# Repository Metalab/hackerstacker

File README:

Hacker Stacker Stacker Hacker
=============

stacker. stacker. STACKER.

You know the game..
Now go build your own with an arduino and 2 x RGB-123
Its fun and addictive.

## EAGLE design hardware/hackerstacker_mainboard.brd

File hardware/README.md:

The eagle files for the mainboard..

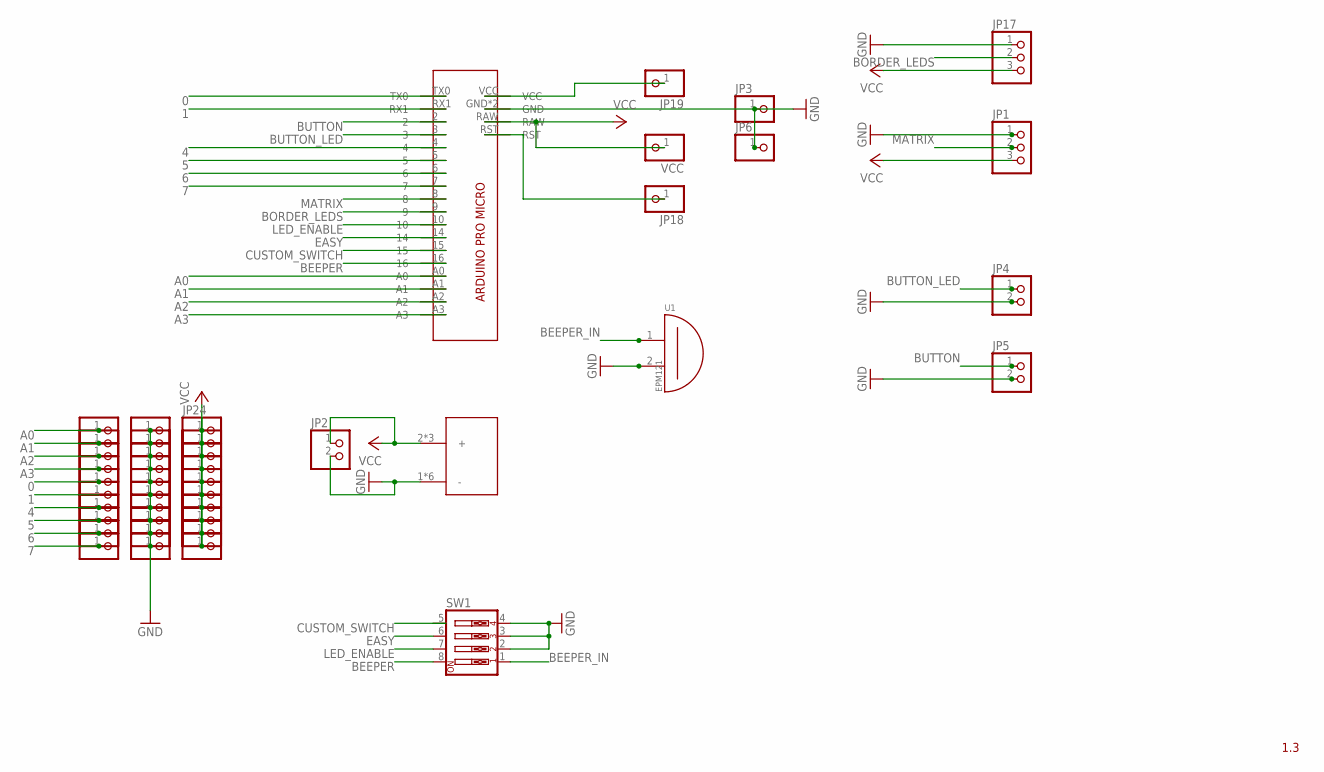
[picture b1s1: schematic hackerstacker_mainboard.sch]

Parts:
JP1, JP17: PINHD-1X3; 1X03
JP2, JP4, JP5: PINHD-1X2; 1X02
JP3, JP6, JP7, JP8, JP9, JP10, JP11, JP12, JP13, JP14, JP15, JP16, JP18, JP19, JP20, JP21, JP22, JP23, JP24, JP25, JP26, JP27, JP28, JP29, JP30, JP31, JP32, JP33, JP34, JP35, JP36, JP37, JP38, JP39: PINHD-1X1CB; 1X01-CLEANBIG
SW1: SW_DIP-4; EDG-04
U1: EPM121
U$1: ARDUINO_PRO_MICRO; APM_PAC
U$3: 2.1MMARDUINOPOERJACK; POWERSUPPLY_DC-21MM
VCC: PINHD-1X1CB; 1X01-CLEANBIG

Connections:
0: JP11.1, U$1.TX0
1: JP12.1, U$1.RX1
4: JP13.1, U$1.4
5: JP37.1, U$1.5
6: JP38.1, U$1.6
7: JP39.1, U$1.7
A0: JP7.1, U$1.A0
A1: JP8.1, U$1.A1
A2: JP9.1, U$1.A2
A3: JP31.1, U$1.A3
BEEPER: SW1.8, U$1.16
BEEPER_IN: SW1.1, U1.1
BORDER_LEDS: JP17.2, U$1.9
BUTTON: JP5.1, U$1.2
BUTTON_LED: JP4.1, U$1.3
CUSTOM_SWITCH: SW1.5, U$1.15
EASY: SW1.6, U$1.14
GND: JP1.1, JP2.2, JP3.1, JP4.2, JP5.2, JP6.1, JP14.1, JP15.1, JP16.1, JP17.1, JP20.1, JP21.1, JP22.1, JP23.1, JP34.1, JP35.1, JP36.1, SW1.2, SW1.3, SW1.4, U1.2, U$1.GND, U$1.GND2 (GND), U$3.1 (-), U$3.3 (-), U$3.4 (-), U$3.5 (-), U$3.6 (-), U$3.7 (-)
LED_ENABLE: SW1.7, U$1.10
MATRIX: JP1.2, U$1.8
unnamed: JP18.1, U$1.RST
unnamed: JP19.1, U$1.VCC
VCC: JP1.3, JP2.1, JP10.1, JP17.3, JP24.1, JP25.1, JP26.1, JP27.1, JP28.1, JP29.1, JP30.1, JP32.1, JP33.1, U$1.RAW, U$3.2 (+), U$3.8 (+), U$3.9 (+), VCC.1

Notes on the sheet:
1.3

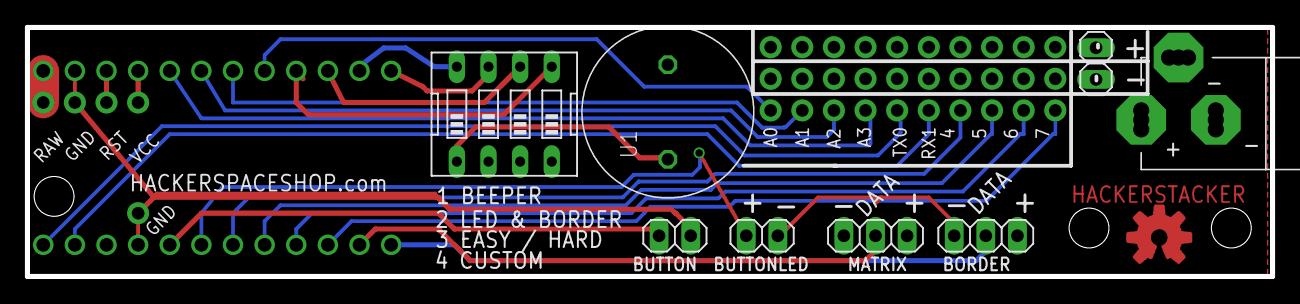
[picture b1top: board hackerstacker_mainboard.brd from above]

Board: 2 copper layers, 100.0 x 20.0 mm, 45 parts (0 on the bottom side), 23 nets.

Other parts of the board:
U$4: OSHWLOGO_TOP_0.2

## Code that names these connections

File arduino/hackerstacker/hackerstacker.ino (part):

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//these pin definitions are valid for arduino pro MICRO (the one with USB

// where is the matrix?
#define MATRIX_PIN 8

// where is the BUTTON?
// needs to be interrupt enabled pin
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#define GAME_BRIGHTNESS 40

// the second dip switch that controls wether the border  and the button should be iluminated or not
#define LED_ENABLE 10

// the third dip switch that controls if the game should be easy or hard TODO: implement this.
#define EASY_HARD 14

// the fourth  dip switch that can be used for custom input .. for example a mode that makes the game unbeatable or something.. 
#define CUSTOM_SWITCH 15

// on board led
#define ONBOARD_LED 17
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// There's only one row here, so it doesn't matter if we declare it in row
// or column order.  The matrices use 800 KHz (v2) pixels that expect GRB
// color data.
Adafruit_NeoMatrix matrix = Adafruit_NeoMatrix(8, 8, 1, 2, MATRIX_PIN,
  NEO_TILE_TOP   + NEO_TILE_LEFT   + NEO_TILE_ROWS   + NEO_TILE_PROGRESSIVE +
  NEO_MATRIX_TOP + NEO_MATRIX_LEFT + NEO_MATRIX_ROWS + NEO_MATRIX_ZIGZAG,
  NEO_GRB + NEO_KHZ800);
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
// dip switched

  pinMode(LED_ENABLE, INPUT_PULLUP);    
  pinMode(EASY_HARD, INPUT_PULLUP);      
  pinMode(CUSTOM_SWITCH, INPUT_PULLUP);  

 
  digitalWrite(BUZZERPIN,LOW);    
  if(!digitalRead(LED_ENABLE)) digitalWrite(LED_PIN,HIGH);    
    
  attachInterrupt(1,buttonpressed_LOW_isr,FALLING);
  
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  button_pressed=1;
  
  
  if(!digitalRead(LED_ENABLE)) analogWrite(LED_PIN, 255);  
    
}

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
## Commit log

2014-11-23 stacker.stacker.stacker!!11
2014-11-23 SOUNDS!
2014-11-23 even more sound.
2014-11-23 harder game by default, added scores
2014-11-23 new highscore system for blocks + rows
2014-11-24 added highscore support in eeprom
2014-11-28 added design fiels for lazzzor + print
2015-09-30 some changes..
2015-09-30 fixed highscore input, added easy/hard mode
2015-09-30 added trollmode on custom switch
2016-10-27 current state of affairs ..

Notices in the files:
arduino/hackerstacker/hackerstacker.ino:
GPL 2.0,  thrown together by overflo from hackerspaceshop.com / metalab.at
